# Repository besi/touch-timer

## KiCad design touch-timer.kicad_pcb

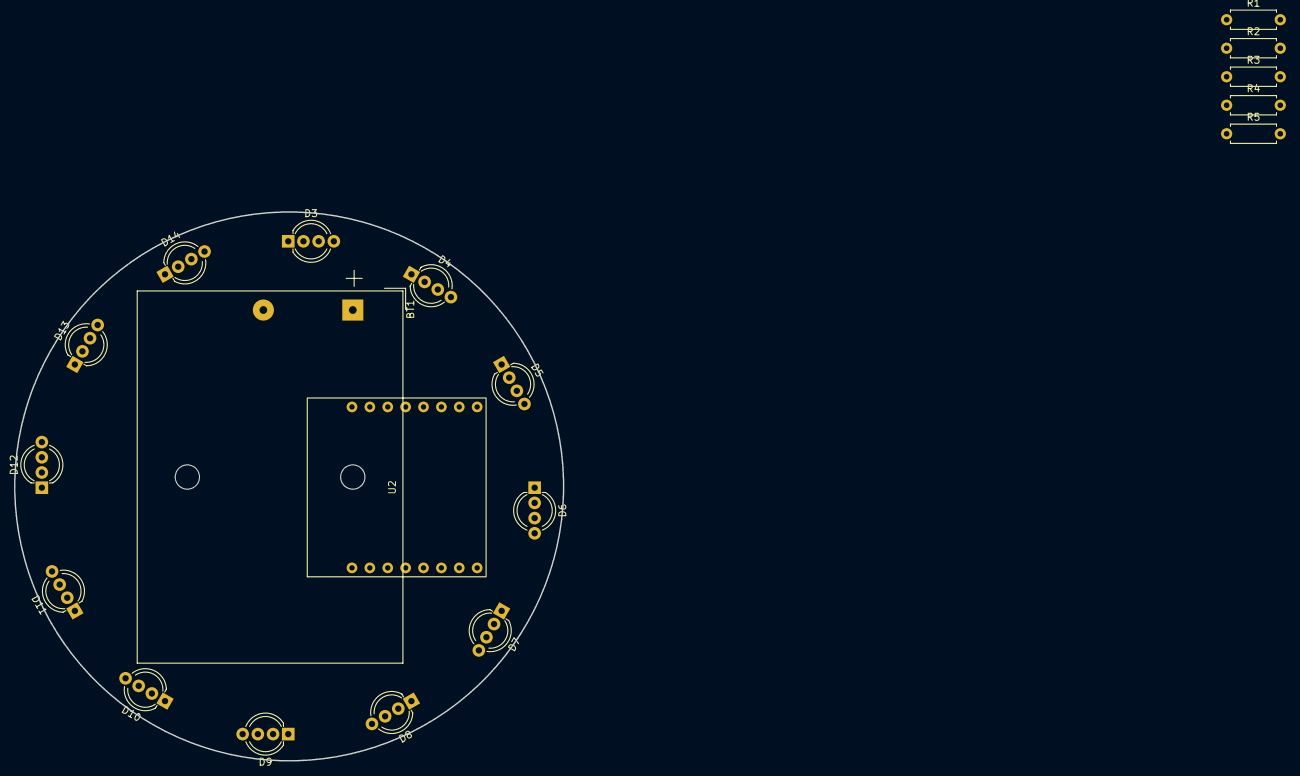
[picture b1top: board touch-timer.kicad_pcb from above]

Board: 2 copper layers, 78.0 x 78.0 mm, 19 parts (0 on the bottom side), 15 nets, no tracks yet.

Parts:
BT1: 3.6V; BatteryHolder_Keystone_2479_3xAAA
D3, D4, D5, D6, D7, D8, D9, D10, D11, D12, D13, D14: NeoPixel_THT; LED_D5.0mm-4_RGB_Wide_Pins
R1: 220k; R_Axial_DIN0207_L6.3mm_D2.5mm_P7.62mm_Horizontal
R2, R3: 100k; R_Axial_DIN0207_L6.3mm_D2.5mm_P7.62mm_Horizontal
R4: 220; R_Axial_DIN0207_L6.3mm_D2.5mm_P7.62mm_Horizontal
R5: 10k; R_Axial_DIN0207_L6.3mm_D2.5mm_P7.62mm_Horizontal
U2: C3 Pico; c3-pico

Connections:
+3V3: D3.2 (VDD), D4.2 (VDD), D5.2 (VDD), D6.2 (VDD), D7.2 (VDD), D8.2 (VDD), D9.2 (VDD), D10.2 (VDD), D11.2 (VDD), D12.2 (VDD), D13.2 (VDD), D14.2 (VDD), R2.1
GND: BT1.2 (-), D3.3 (GND), D4.3 (GND), D5.3 (GND), D6.3 (GND), D7.3 (GND), D8.3 (GND), D9.3 (GND), D10.3 (GND), D11.3 (GND), D12.3 (GND), D13.3 (GND), D14.3 (GND), R1.2, R3.2
unnamed: R3.1, R4.1
unnamed: D3.1 (DOUT), D4.4 (DIN)
unnamed: D4.1 (DOUT), D5.4 (DIN)
unnamed: D5.1 (DOUT), D6.4 (DIN)
unnamed: D6.1 (DOUT), D7.4 (DIN)
unnamed: D7.1 (DOUT), D8.4 (DIN)
unnamed: D8.1 (DOUT), D9.4 (DIN)
unnamed: D9.1 (DOUT), D10.4 (DIN)
unnamed: D10.1 (DOUT), D11.4 (DIN)
unnamed: D11.1 (DOUT), D12.4 (DIN)
unnamed: D12.1 (DOUT), D13.4 (DIN)
unnamed: D13.1 (DOUT), D14.4 (DIN)
Switch: R1.1, R5.1

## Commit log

2024-09-18 Added empty project
2024-09-18 Update pcb with latching circuit, neopixels, wemosd1mini
2024-12-03 Add Lolin C3 and place the leds in a circular fashion
